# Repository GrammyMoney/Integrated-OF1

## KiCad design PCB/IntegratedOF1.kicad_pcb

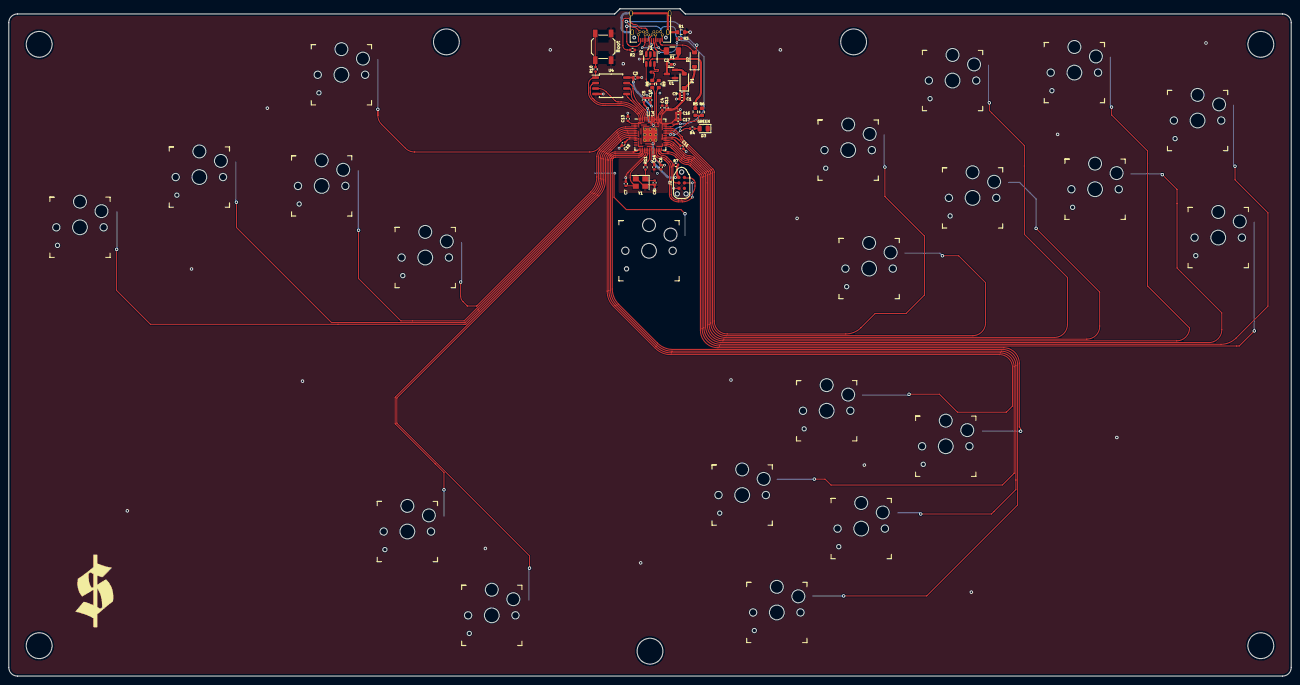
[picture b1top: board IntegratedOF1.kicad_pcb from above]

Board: 2 copper layers, 297.9 x 155.0 mm, 61 parts (0 on the bottom side), 54 nets.

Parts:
C1, C2, C4, C10: 1uF; C_0402_1005Metric
C3, C5, C6, C11, C12, C13, C14, C15, C16, C17: 100nF; C_0402_1005Metric
C7, C8: 22pF; C_0402_1005Metric
C9: 10uF; C_0402_1005Metric
D1, D2: Schottky Diode; D_SOD-123
D3: GREEN; LED_0805_2012Metric
F1: 500 mA; Fuse_1206_3216Metric
J1: USB C Connector; TYPE-C_24P_QCHT
J2: JTAG_TC2030; CON_TC2030_outlined
MX2, MX4, MX4#2, MX5, MX8, MX10, MX12, MX14, MX15, MX17, MX19, MX21, MX23, MX26, MX28, MX29, MX32, MX33, MX36, MX38, MX39: MX_SW_solder; Kailh_socket_PG1350
R1: 1M; R_0603_1608Metric
R2, R3: 5.1k; R_0402_1005Metric
R4: 470; R_0402_1005Metric
R5: 5.6k; R_0603_1608Metric
R6: 10k; R_0603_1608Metric
R7: 10k; R_0402_1005Metric
R8, R9: 27; R_0603_1608Metric
R10, R11: 1k; R_0402_1005Metric
SW1: Boot; SW_SPST_SKQG_WithStem
U1: XC6206; SOT-23
U2: USBLC6-2SC6; SOT-23-6
U3: RP2040; RP2040-QFN-56
U4: W25Q128JVS; SOIC-8_5.23x5.23mm_P1.27mm
Y1: 12MHz; Crystal_SMD_3225-4Pin_3.2x2.5mm

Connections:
3vCable: D2.2 (A), J1.A2 (TX1+), J1.B2 (TX2+)
+1V1: C4.1, C5.1, C6.1, U3.23 (DVDD), U3.45 (VREG_VOUT), U3.50 (DVDD)
+3V3: C1.2, C3.1, C9.1, C10.1, C11.1, C12.1, C13.1, C14.1, C15.1, C16.1, C17.1, D1.1 (K), D2.1 (K), J2.1 (VCC), R7.1, U3.1 (IOVDD), U3.10 (IOVDD), U3.22 (IOVDD), U3.33 (IOVDD), U3.42 (IOVDD), U3.43 (ADC_AVDD), U3.44 (VREG_VIN), U3.48 (USB_VDD), U3.49 (IOVDD), U4.8 (VCC)
+5V: C2.2, F1.2, R5.1, U1.3 (VI), U2.5 (VBUS)
/D_+: R8.2, U3.47 (D+)
/D_-: R9.2, U3.46 (D-)
/XTAL_O: C8.2, R11.1, Y1.1
/~USB_BOOT: R10.1, SW1.2
A: MX36.2, U3.17 (GPIO14)
B: MX19.2, U3.38 (GPIO26/ADC0)
CS: R10.2, U3.56 (QSPI_SS_N), U4.1 (~CS)
C_DN: MX38.2, U3.18 (GPIO15)
C_LT: MX33.2, U3.16 (GPIO13)
C_RT: MX39.2, U3.27 (GPIO16)
C_UP: MX32.2, U3.15 (GPIO12)
D+: R8.1, U2.6 (I/O1)
D-: R9.1, U2.4 (I/O2)
DATA: J1.A11 (RX2+), J1.B11 (RX1+), U3.40 (GPIO28/ADC2)
DBUS+: J1.A6 (D+), J1.B6 (D+), U2.1 (I/O1)
DBUS-: J1.A7 (D-), J1.B7 (D-), U2.3 (I/O2)
DOWN: MX8.2, U3.5 (GPIO3)
GND: C1.1, C2.1, C3.2, C4.2, C5.2, C6.2, C7.1, C8.1, C9.2, C10.2, C11.2, C12.2, C13.2, C14.2, C15.2, C16.2, C17.2, D3.1 (K), J1.A1 (GND), J1.A12 (GND), J1.B1 (GND), J1.B12 (GND), J2.5 (GND), MX2.1, MX4.1, MX4#2.1, MX5.1, MX8.1, MX10.1, MX12.1, MX14.1, MX15.1, MX17.1, MX19.1, MX21.1, MX23.1, MX26.1, MX28.1, MX29.1, MX32.1, MX33.1, MX36.1, MX38.1, MX39.1, R1.1, R2.1, R3.2, R6.2, SW1.1, U1.1 (GND), U2.2 (GND), U3.19 (TESTEN), U3.57 (GND), U4.4 (GND), Y1.2, Y1.4
L: MX4#2.2, U3.7 (GPIO5)
LEFT: MX5.2, U3.6 (GPIO4)
LS: MX15.2, U3.31 (GPIO20)
M1: MX28.2, U3.8 (GPIO6)
M2: MX29.2, U3.9 (GPIO7)
MS: MX17.2, U3.29 (GPIO18)
unnamed: D1.2 (A), U1.2 (VO)
unnamed: D3.2 (A), R4.2
unnamed: F1.1, J1.A4 (VBUS), J1.A9 (VBUS), J1.B4 (VBUS), J1.B9 (VBUS)
unnamed: J1.A5 (CC1), R3.1
unnamed: J1.B5 (CC2), R2.2
unnamed: J1.S1 (SHIELD), R1.2
PICO_LED: R4.1, U3.37 (GPIO25)
QSPI_CLK: U3.52 (QSPI_SCLK), U4.6 (CLK)
R: MX12.2, U3.39 (GPIO27/ADC1)
RIGHT: MX10.2, U3.4 (GPIO2)
SD0: U3.53 (QSPI_SD0), U4.5 (DI(IO0))
SD1: U3.55 (QSPI_SD1), U4.2 (DO(IO1))
SD2: U3.54 (QSPI_SD2), U4.3 (IO2)
SD3: U3.51 (QSPI_SD3), U4.7 (IO3)
START: MX2.2, U3.2 (GPIO0)
SWCLK: J2.4 (SWCLK), U3.24 (SWCLK)
SWD: J2.2 (SWDIO), U3.25 (SWDIO)
UP: MX26.2, U3.28 (GPIO17)
VBUS_SENSE: R5.2, R6.1, U3.36 (GPIO24)
W: MX4.2, U3.3 (GPIO1)
X: MX21.2, U3.32 (GPIO21)
XTAL_IN: C7.2, U3.20 (XTAL_IN), Y1.3
XTAL_OUT: R11.2, U3.21 (XTAL_OUT)
Y: MX14.2, U3.34 (GPIO22)
Z: MX23.2, U3.30 (GPIO19)
~RESET: J2.3 (~RST), R7.2, U3.26 (~RUN)

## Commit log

2023-08-21 Added lite aspects
